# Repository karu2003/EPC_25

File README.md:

# KA30GAN
test project with GAN FET - EPC2021.

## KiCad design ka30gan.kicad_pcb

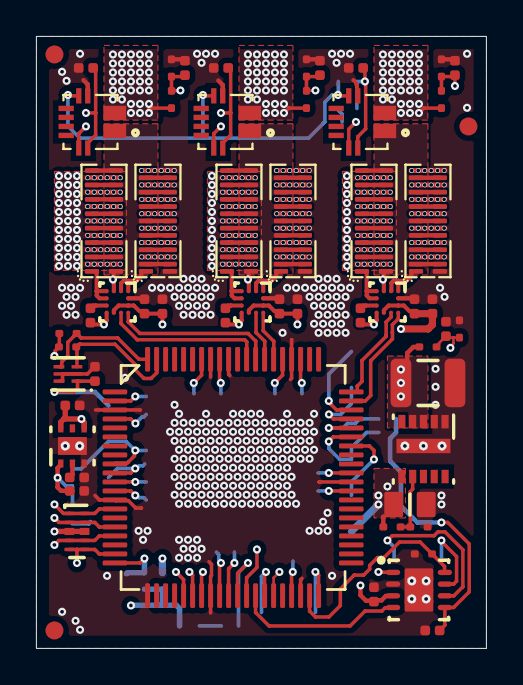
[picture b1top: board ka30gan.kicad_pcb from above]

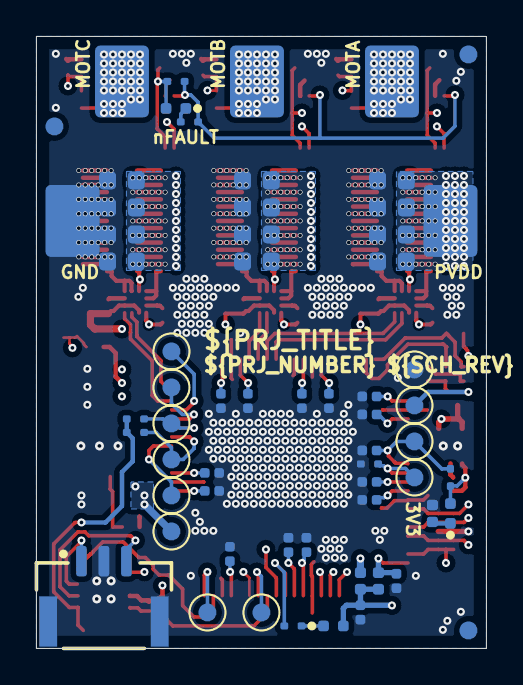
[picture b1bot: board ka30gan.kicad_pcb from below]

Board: 4 copper layers, 25.0 x 34.0 mm, 120 parts (62 on the bottom side), 63 nets.

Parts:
C1A, C1B, C1C, C6A, C6B, C6C, C10, C22, C29, C30, C31A, C31B, C31C, C35, C36: 0.1µF; CAPC1005X05L
C2A, C2B, C2C, C3A, C3B, C3C, C4A, C4B, C4C, C5A, C5B, C5C: 1µF; _Users_Andrew_Documents_Proj_Altium_PCB_Lib_My_PCB.PcbLib_C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
C7, C11, C12, C13, C14, C15, C16, C17, C18, C19, C23, C24, C25, C26, C27, C28: 2.2µF; CAPC1005X05L
C8A, C8B, C8C: 1µF; CAPC1005X05L
C9: 0.01µF; CAPC1005X05L
C20: 10µF; _Users_Andrew_Documents_Proj_Altium_PCB_Lib_Capacitor_AB.DB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
C21: 47µF; _Users_Andrew_Documents_Proj_Altium_PCB_Lib_Capacitor_AB.DB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
C32A, C32B, C32C: 4.7µF; CAPC1005X05L
D1: Red; WL-SMCC_0402 R
D2: TPD4E05U06QDQARQ1; DQA0010A
D3: Green; WL-SMCC_0402 G
D4: Blue; WL-SMCC_0402 B
FID1, FID2, FID3, FID4, FID5, FID6: Fiducial; FIDUCIAL_TOP_C100-200
J1A, J1B, J1C, J4, J5: 2 way net tie junction; J_pin_3x4
L1: BKP1005HS221-T; INDC1005X55N
L2: BLM15PD600SN1D; INDC1005X55N
P1: BM03B-GHS-TBT; JST_BM03B
Q1A, Q1B, Q1C, Q2A, Q2B, Q2C: EPC2021; EPC2X40XL
R1, R4, R5, R12: 2k2; RESC1005X04L
R2, R3: 10k; RESC1005X04L
R6, R8, R10A, R10B, R10C, R16: 4k99; RESC1005X04L
R7, R20: 330 ohm; RESC1005X04L
R9A, R9B, R9C, R14: 47k; RESC1005X04L
R11: 330 ohm; _Users_Andrew_Documents_Proj_Altium_PCB_Lib_Resistor_AB.DbL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
R27: 100k; RESC1005X04L
R28: 24k3; RESC1005X04L
T1, T2, T3, T4, T5, T6, T7, T8, T9, T10, T11, T12: Test_Point_L; TESTPOINT_1
U1A, U1B, U1C: LMG1205YFXR; YFX0012AHAP
U2: LMZM23601SILT; SIL0010A
U3: TMS320F28062FPNT; PN80-L
U4A, U4B, U4C: ACS711KEXLT-31AB-T; ACS711EX
U5: TPS73533DRV; DRV0006A
U6: M24C16-FMH6TG; SON40P170X60-6N
U7: TJA1051TK/3; SON65P300X100_HS-9N

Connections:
3V3: C6A.2, C6B.2, C6C.2, C10.2, C13.2, C19.2, C30.2, C36.2, D1.2, D3.2, D4.2, L1.1, L2.1, R2.2, R3.2, R4.2, R5.2, R6.2, R8.2, T2.1, U3.37, U4A.12, U4B.12, U4C.12, U5.1, U6.1, U7.5
5V: C7.2, C8A.2, C8B.2, C8C.2, C21.2, C32A.2, C32B.2, C32C.2, C35.2, R27.2, T1.1, U1A.A3, U1A.C4, U1B.A3, U1B.C4, U1C.A3, U1C.C4, U2.6, U5.4, U5.6, U7.3
CAN_EN: R12.2, U3.39, U7.8
CAN_H: P1.1, U7.7
CAN_L: P1.3, U7.6
CAN_RX: U3.33, U7.4
CAN_TX: U3.32, U7.1
GND: C2A.1, C2B.1, C2C.1, C3A.1, C3B.1, C3C.1, C4A.1, C4B.1, C4C.1, C5A.1, C5B.1, C5C.1, C6A.1, C6B.1, C6C.1, C7.1, C8A.1, C8B.1, C8C.1, C9.1, C10.1, C11.1, C12.1, C13.1, C14.1, C15.1, C16.1, C17.1, C18.1, C19.1, C20.1, C21.1, C22.1, C23.1, C24.1, C25.1, C26.1, C27.1, C28.1, C29.1, C30.1, C31A.1, C31B.1, C31C.1, C32A.1, C32B.1, C32C.1, C35.1, C36.1, D2.3, D2.8, J5.1, P1.2, P1.16, P1.17, Q2A.2, Q2A.5, Q2A.6, Q2A.9, Q2A.10, Q2A.13, Q2A.14, Q2A.17, Q2A.18, Q2A.21, Q2A.22, Q2A.25, Q2A.26, Q2A.29, Q2A.30, Q2B.2, Q2B.5, Q2B.6, Q2B.9, Q2B.10, Q2B.13, Q2B.14, Q2B.17, Q2B.18, Q2B.21, Q2B.22, Q2B.25, Q2B.26, Q2B.29, Q2B.30, Q2C.2, Q2C.5, Q2C.6, Q2C.9, Q2C.10, Q2C.13, Q2C.14, Q2C.17, Q2C.18, Q2C.21, Q2C.22, Q2C.25, Q2C.26, Q2C.29, Q2C.30, R1.1, R10A.1, R10B.1, R10C.1, R11.1, R12.1, R16.1, R28.1, T11.1, U1A.A2, U1B.A2, U1C.A2, U2.1, U2.2, U2.11, U3.3, U3.13, U3.21, U3.28, U3.38, U3.50, U3.64, U3.71, U3.73, U4A.5, U4B.5, U4C.5, U5.3, U5.7, U6.2, U6.5, U7.2, U7.9
GPIO34: R4.1, T9.1, U3.55
HSA: C1A.2, Q1A.2, Q1A.5, Q1A.6, Q1A.9, Q1A.10, Q1A.13, Q1A.14, Q1A.17, Q1A.18, Q1A.21, Q1A.22, Q1A.25, Q1A.26, Q1A.29, Q1A.30, Q2A.3, Q2A.4, Q2A.7, Q2A.8, Q2A.11, Q2A.12, Q2A.15, Q2A.16, Q2A.19, Q2A.20, Q2A.23, Q2A.24, Q2A.27, Q2A.28, U1A.C1, U1A.D4, U4A.1
HSB: C1B.2, Q1B.2, Q1B.5, Q1B.6, Q1B.9, Q1B.10, Q1B.13, Q1B.14, Q1B.17, Q1B.18, Q1B.21, Q1B.22, Q1B.25, Q1B.26, Q1B.29, Q1B.30, Q2B.3, Q2B.4, Q2B.7, Q2B.8, Q2B.11, Q2B.12, Q2B.15, Q2B.16, Q2B.19, Q2B.20, Q2B.23, Q2B.24, Q2B.27, Q2B.28, U1B.C1, U1B.D4, U4B.1
HSC: C1C.2, Q1C.2, Q1C.5, Q1C.6, Q1C.9, Q1C.10, Q1C.13, Q1C.14, Q1C.17, Q1C.18, Q1C.21, Q1C.22, Q1C.25, Q1C.26, Q1C.29, Q1C.30, Q2C.3, Q2C.4, Q2C.7, Q2C.8, Q2C.11, Q2C.12, Q2C.15, Q2C.16, Q2C.19, Q2C.20, Q2C.23, Q2C.24, Q2C.27, Q2C.28, U1C.C1, U1C.D4, U4C.1
INH_A: U1A.B4, U3.69
INH_B: U1B.B4, U3.67
INH_C: U1C.B4, U3.60
INL_A: U1A.A4, U3.68
INL_B: U1B.A4, U3.66
INL_C: U1C.A4, U3.59
I_A: U3.27, U4A.11
I_B: U3.26, U4B.11
I_C: U3.25, U4C.11
LED: R20.1, U3.31
NFAULT: R3.1, R7.1, U3.35, U4A.6, U4B.6, U4C.6
NRESET: C29.2, R2.1, T12.1, U3.9
NetC1A_1: C1A.1, U1A.D3
NetC1B_1: C1B.1, U1B.D3
NetC1C_1: C1C.1, U1C.D3
NetC9_2: C9.2, U5.2
NetC12_2: C12.2, U3.2
NetC14_2: C14.2, U3.12
NetC15_2: C15.2, U3.29
NetC16_2: C16.2, U3.51
NetC17_2: C17.2, U3.65
NetC18_2: C18.2, U3.72
NetD1_1: D1.1, R7.2
NetD3_1: D3.1, R11.2
NetD4_1: D4.1, R20.2
NetQ1A_1: Q1A.1, U1A.D1, U1A.D2
NetQ1B_1: Q1B.1, U1B.D1, U1B.D2
NetQ1C_1: Q1C.1, U1C.D1, U1C.D2
NetQ2A_1: Q2A.1, U1A.A1, U1A.B1
NetQ2B_1: Q2B.1, U1B.A1, U1B.B1
NetQ2C_1: Q2C.1, U1C.A1, U1C.B1
NetR27_1: R27.1, R28.2, U2.7
PHA: J1A.1, R9A.2, U4A.3
PHB: J1B.1, R9B.2, U4B.3
PHC: J1C.1, R9C.2, U4C.3
PVDD: C2A.2, C2B.2, C2C.2, C3A.2, C3B.2, C3C.2, C4A.2, C4B.2, C4C.2, C5A.2, C5B.2, C5C.2, C20.2, J4.1, Q1A.3, Q1A.4, Q1A.7, Q1A.8, Q1A.11, Q1A.12, Q1A.15, Q1A.16, Q1A.19, Q1A.20, Q1A.23, Q1A.24, Q1A.27, Q1A.28, Q1B.3, Q1B.4, Q1B.7, Q1B.8, Q1B.11, Q1B.12, Q1B.15, Q1B.16, Q1B.19, Q1B.20, Q1B.23, Q1B.24, Q1B.27, Q1B.28, Q1C.3, Q1C.4, Q1C.7, Q1C.8, Q1C.11, Q1C.12, Q1C.15, Q1C.16, Q1C.19, Q1C.20, Q1C.23, Q1C.24, Q1C.27, Q1C.28, R14.2, U2.3, U2.4
SCI_RX_in: T3.1, U3.40
SCI_TX_out: T4.1, U3.34
SCL: R6.1, U3.80, U6.4
SDA: R8.1, U3.79, U6.3
TCK: T6.1, U3.54
TDI: T8.1, U3.57
TDO: R5.1, T10.1, U3.56
TMS: T7.1, U3.58
VDDA: C11.2, L1.2, U3.20
VDDIO: C23.2, C24.2, C25.2, C26.2, C27.2, C28.2, L2.2, U3.4, U3.11, U3.30, U3.49, U3.63, U3.74
VSEN_PVDD: C22.2, D2.5, D2.6, R14.1, R16.2, U3.19
V_A: C31A.2, D2.1, D2.10, R9A.1, R10A.2, U3.14
V_B: C31B.2, D2.2, D2.9, R9B.1, R10B.2, U3.16
V_C: C31C.2, D2.4, D2.7, R9C.1, R10C.2, U3.17
nTRST: R1.2, T5.1, U3.10

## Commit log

2023-11-10 rename project
2023-11-10 edit sym
2023-11-10 fix DRC
2023-11-10 add 3d models
